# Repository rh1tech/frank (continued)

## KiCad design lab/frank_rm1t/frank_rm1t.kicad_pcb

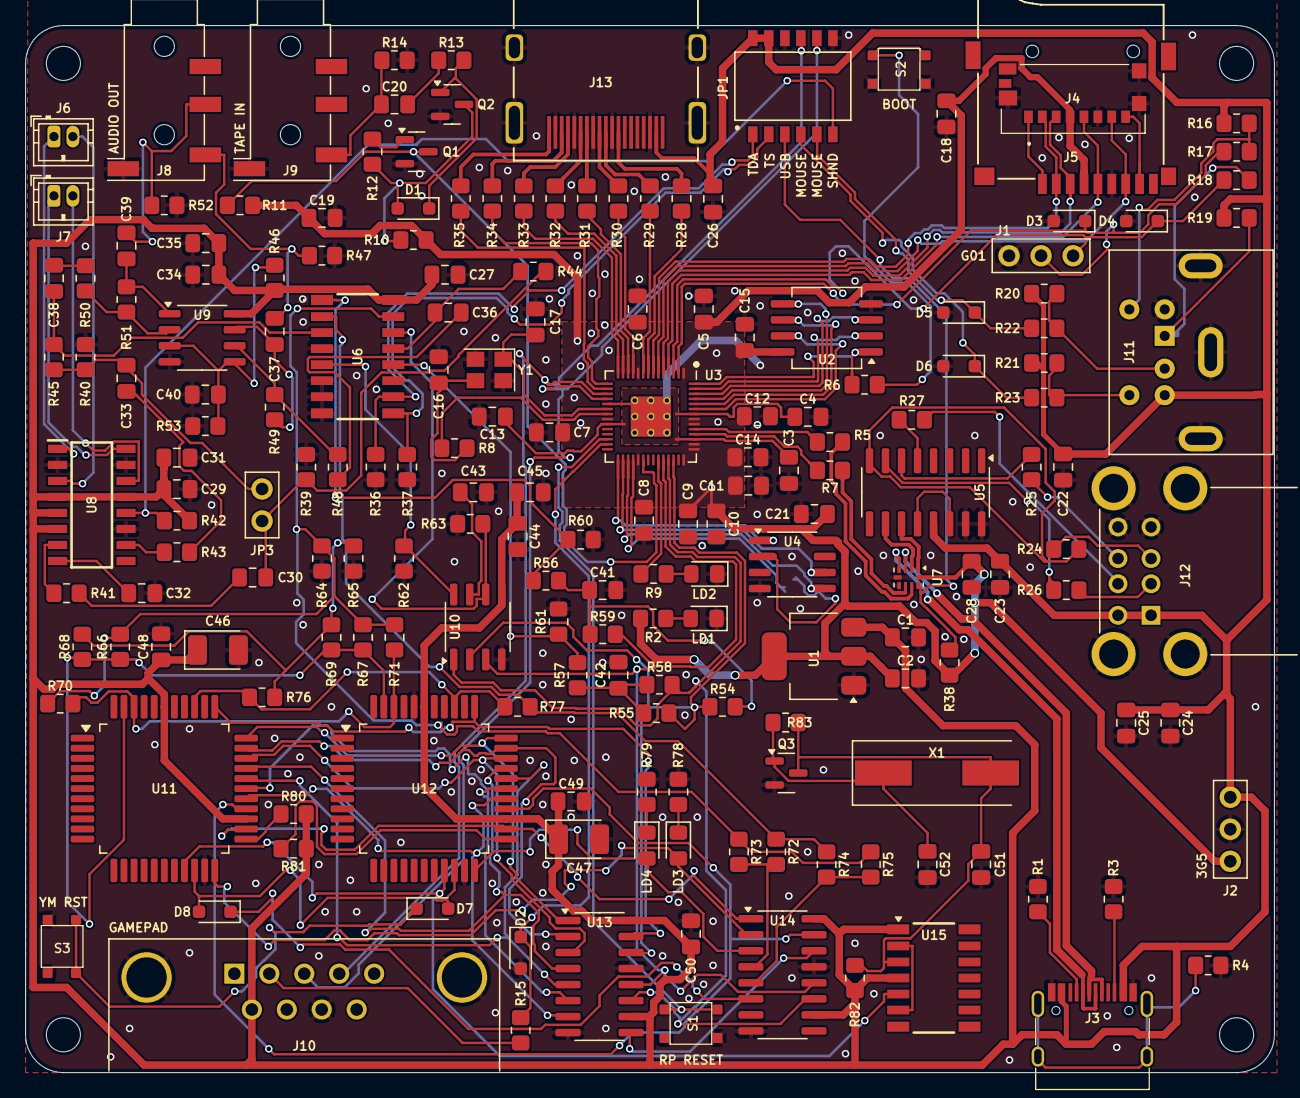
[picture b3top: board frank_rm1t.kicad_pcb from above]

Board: 2 copper layers, 99.0 x 83.0 mm, 190 parts (1 on the bottom side), 150 nets.

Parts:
C1, C2, C24, C25, C34, C36, C37, C38, C39, C40, C43, C44: 10u; Capacitor (0805)
C3, C4, C5, C6, C7, C8, C9, C10, C11, C12, C15, C18, C19, C20, C21, C22, C26, C27, C28, C32, C35, C45, C48, C49, C50: 100n; Capacitor (0805)
C13, C14, C29, C30, C33: 1u; Capacitor (0805)
C16, C17: 15p; Capacitor (0805)
C23: 4.7u; Capacitor (0805)
C31: 47u; Capacitor (0805)
C41, C42: 47n; Capacitor (0805)
C46, C47: 100u; Capacitor (3528, tantalum, polar)
C51, C52: 22p; Capacitor (0805)
D1, D7, D8: 1N4148; Diode (SOD-323)
D2, D3, D4, D5, D6: 3V3; Diode (SOD-323)
H1, H2, H3, H4: MountingHole; Mounting Hole (2.7mm)
J1: UART; Pin Header (1x03)
J2: PWR; Pin Header (1x03)
J3: USB4215-03-A; USB Type C
J4: 0475710001; MicroSD (SMD, short)
J5: 104031-0811; MicroSD (SMD, long)
J6: PAM L; Connector Female ZH 1.50mm (2 pins)
J7: PAM R; Connector Female ZH 1.50mm (2 pins)
J8, J9: PJ-320D; Jack (3.5mm, PJ-320D)
J10: D-SUB 9 Male; D-SUB (9 pin, male, top mount)
J11: MDC-036; MiniDIN (6 Pin, female)
J12: SS-52100-004; USB Type A (stacked)
J13: DC3RX19JA2; HDMI (female)
JP1: Main Jumpers; SW_DS05-127-2-06BK-SMT-TR
JP2: Jumper (Solder); Jumper (solder)
JP3: Mono; Pin Header (1x02)
LD1: Green; LED (0805)
LD2: Blue; LED (0805)
LD3, LD4: Orange; LED (0805)
Q1, Q2, Q3: BC850; SOT-23
R1, R3: 5.1K; Resistor (0805)
R2, R6, R8, R9, R11, R15, R16, R19, R20, R21, R58, R59, R78, R79, R80, R81, R82: 1K; Resistor (0805)
R4: 1M; Resistor (0805)
R5, R7: 27R; Resistor (0805)
R10, R12, R13, R36, R37, R38, R41, R42, R43, R44, R45, R46, R48, R50, R53, R56, R57, R72, R73, R74, R75: 10K; Resistor (0805)
R14, R17, R18, R22, R23: 100R; Resistor (0805)
R24, R25, R26, R27: 22R; Resistor (0805)
R28, R29, R30, R31, R32, R33, R34, R35: 270R; Resistor (0805)
R39, R40, R54, R55, R60, R61, R68, R69, R70, R71: 2K; Resistor (0805)
R47, R52: 20K; Resistor (0805)
R49, R51: 47K; Resistor (0805)
R62, R63: 470R; Resistor (0805)
R64, R65: 120R; Resistor (0805)
R66, R67, R76, R77: 4.7K; Resistor (0805)
R83: 100K; Resistor (0805)
S1: Reset; Button (SMD, 3x3mm, 1-1)
S2: Boot; Button (SMD, 3x3mm, 1-1)
S3: KLS7-TS3302; Button (SMD, 3x3mm, 1-1)
U1: NCP1117 3.3; SOT-223
U2: W25Q128JVSIQ; SOIC-8
U3: RP2040; QFN 56
U4: ESP-PSRAM32; SO-8
U5: MW7211A; SOP-16
U6: 74HC4052D; 74HC4052D653
U7: TS3USB221RSER; UQFN-10
U8: PAM8403D; SOIC127P600X175-16N
U9: LM358; SO-8
U10: TDA1387T; SO-8
U11, U12: YM3439-F
U13, U14: 74HC595; SOP-16
U15: 74HC74; 74HCT74D
X1: 3.58 MHz; Crystal (HC49-S)
Y1: 12 MHz; Crystal (3225)

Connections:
+3V3: C2.1, C5.1, C6.1, C7.1, C8.1, C9.1, C10.1, C11.1, C12.1, C14.1, C15.1, C18.2, C19.1, C21.1, C28.2, J2.1, J4.P4 (VDD), J5.4 (VDD), R2.2, R10.1, R11.1, R38.1, U1.2 (VO), U2.8 (VCC), U3.1 (IOVDD), U3.10 (IOVDD), U3.22 (IOVDD), U3.33 (IOVDD), U3.42 (IOVDD), U3.43 (ADC_AVDD), U3.44 (VREG_IN), U3.48 (USB_VDD), U3.49 (IOVDD), U4.8 (VCC), U7.10 (VCC)
/AMP_IN_L: C36.1, R44.1, U6.13 (1Z)
/AMP_IN_R: C38.1, R45.1, U6.3 (2Z)
/Audio Out/AMP_OUTL: C37.2, J8.T, R47.2
/Audio Out/AMP_OUTR: C39.2, J8.R, R52.2
/Audio Out/AMP_PAM_OUTL_M: J6.2, U8.3 (-OUTL)
/Audio Out/AMP_PAM_OUTL_P: J6.1, U8.1 (+OUT_L)
/Audio Out/AMP_PAM_OUTR_M: J7.2, U8.14 (-OUT_R)
/Audio Out/AMP_PAM_OUTR_P: J7.1, U8.16 (+OUT_R)
/Audio Out/Amplifier/ MONO_L: C30.1, JP3.1, R39.1, R44.2
/Audio Out/Amplifier/MONO_R: C33.1, JP3.2, R40.1, R45.2
/Audio Out/TS/A1: R66.2, R67.2, R68.2, R69.2, U11.43 (CHA), U12.43 (CHA)
/Audio Out/TS/B1: R70.2, R71.2, U11.42 (CHB), U12.42 (CHB)
/Audio Out/TS/BEEP: R72.2, R73.2, U14.4 (QE)
/Audio Out/TS/C1: R76.2, R77.2, U11.36 (CHC), U12.36 (CHC)
/Audio Out/TS/CLK_1.75M: U11.19 (CLOCK), U12.19 (CLOCK), U15.5 (Q)
/Audio Out/TS/DA0: U11.34 (DA0), U12.34 (DA0), U13.15 (QA)
/Audio Out/TS/DA1: U11.33 (DA1), U12.33 (DA1), U13.1 (QB)
/Audio Out/TS/DA2: U11.32 (DA2), U12.32 (DA2), U13.2 (QC)
/Audio Out/TS/DA3: U11.31 (DA3), U12.31 (DA3), U13.3 (QD)
/Audio Out/TS/DA4: U11.30 (DA4), U12.30 (DA4), U13.4 (QE)
/Audio Out/TS/DA5: U11.29 (DA5), U12.29 (DA5), U13.5 (QF)
/Audio Out/TS/DA6: U11.28 (DA6), U12.28 (DA6), U13.6 (QG)
/Audio Out/TS/DA7: U11.27 (DA7), U12.27 (DA7), U13.7 (QH)
/Audio Out/TS/SAVE: R74.2, R75.2, U14.5 (QF)
/Audio Out/TS/YM_BC1: U11.26 (BC1), U12.26 (BC1), U14.15 (QA)
/Audio Out/TS/YM_BDIR: U11.24 (BDIR), U12.24 (BDIR), U14.1 (QB)
/Audio Out/TS/YM_CS1: LD3.2 (A), U11.22 (A8), U14.2 (QC)
/Audio Out/TS/YM_CS2: LD4.2 (A), U12.22 (A8), U14.3 (QD)
/Audio Out/TS/YM_RST: D7.2 (A), D8.2 (A), U11.20 (RESET), U12.20 (RESET)
/Audio Out/TS/YM_SEL1: R80.2, U11.23 (SEL)
/Audio Out/TS/YM_SEL2: R81.2, U12.23 (SEL)
/D+: R5.1, U7.8 (D+)
/D-: R7.1, U7.7 (D-)
/DAT1: J4.P8 (DAT1), J5.8 (DAT1)
/DAT2: J4.P1 (DAT2), J5.1 (DAT2)
/GPIO0: D3.1 (K), J1.2, R17.2, U3.2 (GPIO0)
/GPIO1: D4.1 (K), J1.3, R18.2, U3.3 (GPIO1)
/GPIO2: J4.P5 (CLK), J5.5 (CLK), U3.4 (GPIO2)
/GPIO3: J4.P3 (CMD), J5.3 (CMD), U3.5 (GPIO3)
/GPIO4: J4.P7 (DAT0), J5.7 (DAT0), U3.6 (GPIO4)
/GPIO5: J4.P2 (CD/DAT3), J5.2 (DAT3/CD), U3.7 (GPIO5)
/GPIO6: R28.2, U3.8 (GPIO6)
/GPIO7: R29.2, U3.9 (GPIO7)
/GPIO8: R30.2, U3.11 (GPIO8)
/GPIO9: R31.2, U3.12 (GPIO9)
/GPIO10: R32.2, U3.13 (GPIO10)
/GPIO11: R33.2, U3.14 (GPIO11)
/GPIO12: R34.2, U3.15 (GPIO12)
/GPIO13: R35.2, U3.16 (GPIO13)
/GPIO14: J10.4, JP1.9, U3.17 (GPIO14)
/GPIO15: J10.3, JP1.8, U3.18 (GPIO15)
/GPIO16: D2.1 (K), R15.1, U3.27 (GPIO16)
/GPIO18: U3.29 (GPIO18), U4.1 (~CE)
/GPIO19: U3.30 (GPIO19), U4.6 (SCLK)
/GPIO20: U3.31 (GPIO20), U4.5 (SI/SIO)
/GPIO21: JP2.2 (B), U3.32 (GPIO21)
/GPIO22: Q1.3 (C), R11.2, U3.34 (GPIO22)
/GPIO26: R59.2, U3.38 (GPIO26_ADC0), U10.3 (DATA), U13.12 (RCLK), U14.12 (RCLK)
/GPIO27: R58.2, U3.39 (GPIO27_ADC1), U10.1 (SCLK), U13.11 (SRCLK), U14.11 (SRCLK)
/GPIO28: R54.1, R55.1, U3.40 (GPIO28_ADC2), U10.2 (LRCK), U13.14 (SER)
/HUB_D+: U5.11 (DPU), U7.1 (1D+)
/HUB_D-: U5.10 (DMU), U7.2 (1D-)
/J_TDA: JP1.1, R36.2, U6.10 (S0)
/J_TS: JP1.2, R37.2, U6.9 (S1)
/KB_CLK: J11.5, R16.2, R17.1
/KB_DATA: J11.1, R18.1, R19.2
/MS_CLK: J11.6, R21.2, R23.1
/MS_CLK_3V: D6.1 (K), JP1.4, R23.2
/MS_DATA: J11.2, R20.2, R22.1
/MS_DATA_3V: D5.1 (K), JP1.5, R22.2
/PWM_OUT_L: R57.2, R61.1, U6.12 (1Y0)
/PWM_OUT_R: R56.2, R60.1, U6.1 (2Y0)
/RP2040/GPIO25: R9.2, U3.37 (GPIO25)
/RP2040/QSPI_SCLK: U2.6 (CLK), U3.52 (QSPI_SCLK)
/RP2040/QSPI_SD0: U2.5 (DI(IO0)), U3.53 (QSPI_SD0)
/RP2040/QSPI_SD1: U2.2 (DO(IO1)), U3.55 (QSPI_SD1)
/RP2040/QSPI_SD2: U2.3 (IO2), U3.54 (QSPI_SD2)
/RP2040/QSPI_SD3: U2.7 (IO3), U3.51 (QSPI_SD3)
/RP2040/QSPI_SS: R6.1, U2.1 (~CS), U3.56 (QSPI_SS)
/RP2040/XIN: C17.1, U3.20 (XIN), Y1.1
/RP2040/XOUT: R8.1, U3.21 (XOUT)
/RUN: S1.1, U3.26 (RUN)
/SHND: JP1.6, R42.2, U8.12 (SHND)
/TDA_L: R63.2, U6.14 (1Y1), U10.6 (A_LEFT)
/TDA_R: R62.1, U6.5 (2Y1), U10.8 (A_RIGHT)
/TS_L: R64.1, R66.1, R67.1, R70.1, R71.1, R73.1, R75.1, U6.15 (1Y2)
/TS_R: R65.1, R68.1, R69.1, R72.1, R74.1, R76.1, R77.1, U6.2 (2Y2)
/USBMPXSW: JP1.3, R38.2, U7.9 (S)
/USB_D1+: R24.1, U5.8 (DP3)
/USB_D1-: R26.1, U5.7 (DM3)
/USB_D2+: R25.1, U5.6 (DP2)
/USB_D2-: R27.1, U5.5 (DM2)
/UTC_D+: J3.6 (DP1), J3.8 (DP2), U7.3 (2D+)
/UTC_D-: J3.5 (DN2), J3.7 (DN1), U7.4 (2D-)
GND: C1.2, C2.2, C3.2, C4.2, C5.2, C6.2, C7.2, C8.2, C9.2, C10.2, C11.2, C12.2, C13.2, C14.2, C15.2, C16.2, C17.2, C18.1, C19.2, C21.2, C22.2, C23.2, C24.2, C25.2, C26.2, C27.1, C28.1, C29.2, C31.2, C32.2, C34.1, C35.1, C40.1, C41.2, C42.2, C43.2, C44.2, C45.2, C46.2, C47.2, C48.2, C49.2, C50.2, C51.1, C52.1, D2.2 (A), D3.2 (A), D4.2 (A), D5.2 (A), D6.2 (A), J1.1, J2.2, J3.1 (GND), J3.12 (GND), J4.G1 (GND_1), J4.G2 (GND_2), J4.G3 (GND_3), J4.P6 (VSS), J5.6 (VSS), J8.S, J9.S, J10.8, J11.3, J12.4 (GND1), J12.8 (GND2), J12.9 (Shield), J13.2 (G_D2), J13.5 (G_D1), J13.8 (G_D0), J13.11 (G_CLK), J13.17 (G_DDC/CEC), J13.20 (SHIELD1), J13.21 (SHIELD2), J13.22 (SHIELD3), J13.23 (SHIELD4), JP1.7, JP1.10, LD1.1 (K), LD2.1 (K), Q1.2 (E), Q2.2 (E), Q3.2 (E), R1.1, R3.1, R4.2, R14.2, R36.1, R37.1, R39.2, R40.2, R47.1, R52.1, R53.1, R60.2, R61.2, R62.2, R63.1, R64.2, R65.2, R78.1, R79.1, S1.2, S2.2, S3.2, U1.1 (GND), U2.4 (GND), U3.19 (TESTEN), U3.57 (GND), U4.4 (VSS), U5.15 (GND), U5.16 (GND), U6.4 (2Y3), U6.6 (~E), U6.7 (VEE), U6.8 (GND), U6.11 (1Y3), U7.5 (GND), U7.6 (~OE), U8.2 (PGND), U8.11 (GND), U8.15 (PGND), U9.4 (V-), U10.4 (AGND), U11.21 (A9), U11.40 (VSS), U12.21 (A9), U12.40 (VSS), U13.8 (GND), U13.13 (~OE), U14.8 (GND), U14.13 (~OE), Y1.2, Y1.4
unnamed: C16.1, R8.2, Y1.3
unnamed: C20.1, J9.T, R14.1
unnamed: C20.2, R13.1
unnamed: C30.2, R41.2
unnamed: C33.2, R43.2
unnamed: C36.2, R48.2
unnamed: C37.1, R49.1, U9.7
unnamed: C38.2, R50.2
unnamed: C39.1, R51.1, U9.1
unnamed: C41.1, R54.2, R56.1, R59.1
unnamed: C42.1, R55.2, R57.1, R58.1
unnamed: D1.2 (A), Q2.3 (C), R10.2, R12.1
unnamed: D1.1 (K), Q2.1 (B), R13.2
unnamed: D7.1 (K), S3.1
unnamed: D8.1 (K), U14.6 (QG)
unnamed: J3.4 (CC1), R1.2
unnamed: J3.10 (CC2), R3.2
unnamed: J3.13 (SHIELD), R4.1
unnamed: J10.2, R15.2
unnamed: J12.3 (D1+), R24.2
unnamed: J12.2 (D1-), R26.2
unnamed: J12.7 (D2+), R25.2
unnamed: J12.6 (D2-), R27.2
unnamed: J13.12 (CLKN), R28.1
unnamed: J13.10 (CLKP), R29.1
unnamed: J13.9 (D0N), R30.1
unnamed: J13.7 (D0P), R31.1
unnamed: J13.6 (D1N), R32.1
unnamed: J13.4 (D1P), R33.1
unnamed: J13.3 (D2N), R34.1
unnamed: J13.1 (D2P), R35.1
unnamed: JP2.1 (A), U4.2 (SO/SIO)
unnamed: LD1.2 (A), R2.1
unnamed: LD2.2 (A), R9.1
unnamed: LD3.1 (K), R78.2
unnamed: LD4.1 (K), R79.2
unnamed: Q1.1 (B), R12.2
unnamed: C52.2, Q3.1 (B), R83.1, X1.1
unnamed: C51.2, Q3.3 (C), R82.1, R83.2, U15.3 (C), X1.2
unnamed: R6.2, S2.1
unnamed: R7.2, U3.46 (USB_DM)
unnamed: R5.2, U3.47 (USB_DP)
unnamed: C3.1, C4.1, C13.1, U3.23 (DVDD), U3.45 (VREG_VOUT), U3.50 (DVDD)
unnamed: U5.12 (VD33), U5.14 (VD3)
unnamed: R41.1, U8.7 (INL)
unnamed: R43.1, U8.10 (INR)
unnamed: C32.1, U8.8 (VREF)
unnamed: C40.2, R46.1, R53.2, U9.3 (+), U9.5 (+)
unnamed: R50.1, R51.2, U9.2 (-)
unnamed: R48.1, R49.2, U9.6 (-)
unnamed: C43.1, U10.7 (FLT)
unnamed: U13.9 (QH'), U14.14 (SER)
unnamed: U15.2 (D), U15.6 (~Q)
VBUS: C1.1, C22.1, C23.1, C24.1, C25.1, C26.1, C27.2, C29.1, C31.1, C34.2, C35.2, C44.1, C45.1, C46.1, C47.1, C48.1, C49.1, C50.1, J2.3, J3.2 (VBUS), J3.11 (VBUS), J10.6, J11.4, J12.1 (VBUS1), J12.5 (VBUS2), J13.18 (+5V), JP1.11, JP1.12, R16.1, R19.1, R20.1, R21.1, R42.1, R46.2, R80.1, R81.1, R82.2, U1.3 (VI), U5.13 (VDD5), U6.16 (VCC), U8.4 (PVDD), U8.5 (MUTE), U8.6 (VDD), U8.13 (PVDD), U9.8 (V+), U10.5 (VA), U11.25 (BC2), U11.39 (VDD), U12.25 (BC2), U12.39 (VDD), U13.10 (~SRCLR), U13.16 (VCC), U14.10 (~SRCLR), U14.16 (VCC), U15.1 (~R), U15.4 (~S)

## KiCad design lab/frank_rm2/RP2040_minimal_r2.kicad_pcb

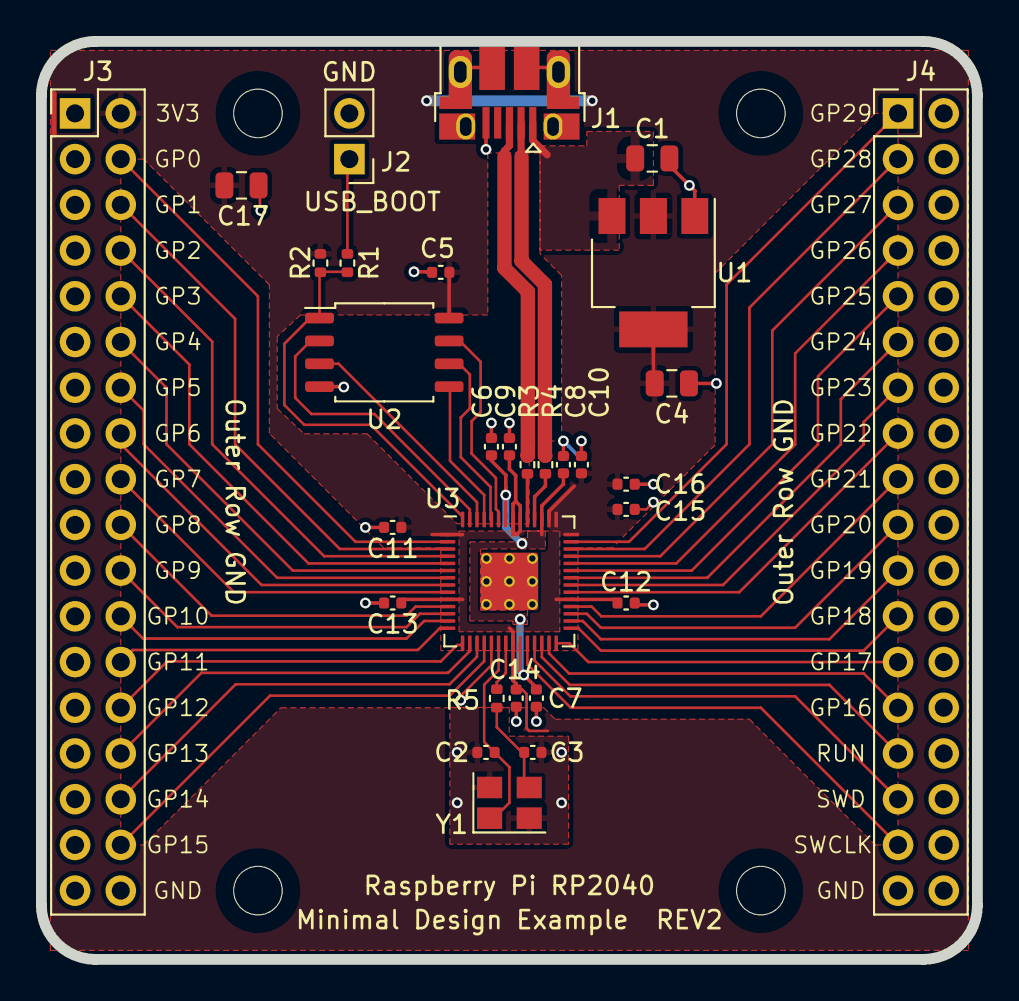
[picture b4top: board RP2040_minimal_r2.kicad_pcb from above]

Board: 2 copper layers, 52.0 x 51.0 mm, 34 parts (0 on the bottom side), 51 nets.

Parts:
C1, C4, C17: 10u; C_0805_2012Metric
C2, C3: 15p; C_0402_1005Metric
C5, C6, C7, C9, C11, C12, C13, C14, C15, C16: 100n; C_0402_1005Metric
C8, C10: 1u; C_0402_1005Metric
H1, H2, H3, H4: MountingHole; MountingHole_2.7mm_M2.5
J1: USB_B_Micro; USB_Micro-B_Amphenol_10103594-0001LF_Horizontal_modified
J2: Conn_01x02; PinHeader_1x02_P2.54mm_Vertical
J3, J4: Conn_02x18_Odd_Even; PinHeader_2x18_P2.54mm_Vertical
R1, R5: 1k; R_0402_1005Metric
R2: DNF; R_0402_1005Metric
R3, R4: 27; R_0402_1005Metric
U1: NCP1117-3.3_SOT223; SOT-223-3_TabPin2
U2: W25Q128JVS; SOIC-8_5.23x5.23mm_P1.27mm
U3: RP2040; RP2040-QFN-56
Y1: ABM8-272-T3; Crystal_SMD_3225-4Pin_3.2x2.5mm

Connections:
+1V1: C6.1, C7.1, C8.1, U3.23 (DVDD), U3.45 (VREG_VOUT), U3.50 (DVDD)
+3V3: C4.1, C5.1, C9.1, C10.1, C11.1, C12.1, C13.1, C14.1, C15.1, C16.1, C17.1, J3.2, R2.1, U1.2 (VO), U2.8 (VCC), U3.1 (IOVDD), U3.10 (IOVDD), U3.22 (IOVDD), U3.33 (IOVDD), U3.42 (IOVDD), U3.43 (ADC_AVDD), U3.44 (VREG_IN), U3.48 (USB_VDD), U3.49 (IOVDD)
/GPIO0: J3.4, U3.2 (GPIO0)
/GPIO1: J3.6, U3.3 (GPIO1)
/GPIO2: J3.8, U3.4 (GPIO2)
/GPIO3: J3.10, U3.5 (GPIO3)
/GPIO4: J3.12, U3.6 (GPIO4)
/GPIO5: J3.14, U3.7 (GPIO5)
/GPIO6: J3.16, U3.8 (GPIO6)
/GPIO7: J3.18, U3.9 (GPIO7)
/GPIO8: J3.20, U3.11 (GPIO8)
/GPIO9: J3.22, U3.12 (GPIO9)
/GPIO10: J3.24, U3.13 (GPIO10)
/GPIO11: J3.26, U3.14 (GPIO11)
/GPIO12: J3.28, U3.15 (GPIO12)
/GPIO13: J3.30, U3.16 (GPIO13)
/GPIO14: J3.32, U3.17 (GPIO14)
/GPIO15: J3.34, U3.18 (GPIO15)
/GPIO16: J4.27, U3.27 (GPIO16)
/GPIO17: J4.25, U3.28 (GPIO17)
/GPIO18: J4.23, U3.29 (GPIO18)
/GPIO19: J4.21, U3.30 (GPIO19)
/GPIO20: J4.19, U3.31 (GPIO20)
/GPIO21: J4.17, U3.32 (GPIO21)
/GPIO22: J4.15, U3.34 (GPIO22)
/GPIO23: J4.13, U3.35 (GPIO23)
/GPIO24: J4.11, U3.36 (GPIO24)
/GPIO25: J4.9, U3.37 (GPIO25)
/GPIO26_ADC0: J4.7, U3.38 (GPIO26_ADC0)
/GPIO27_ADC1: J4.5, U3.39 (GPIO27_ADC1)
/GPIO28_ADC2: J4.3, U3.40 (GPIO28_ADC2)
/GPIO29_ADC3: J4.1, U3.41 (GPIO29_ADC3)
/QSPI_SCLK: U2.6 (CLK), U3.52 (QSPI_SCLK)
/QSPI_SD0: U2.5 (DI(IO0)), U3.53 (QSPI_SD0)
/QSPI_SD1: U2.2 (DO(IO1)), U3.55 (QSPI_SD1)
/QSPI_SD2: U2.3 (IO2), U3.54 (QSPI_SD2)
/QSPI_SD3: U2.7 (IO3), U3.51 (QSPI_SD3)
/QSPI_SS: R1.1, R2.2, U2.1 (~CS), U3.56 (QSPI_SS)
/RUN: J4.29, U3.26 (RUN)
/SWCLK: J4.33, U3.24 (SWCLK)
/SWD: J4.31, U3.25 (SWD)
/USB_D+: J1.3 (D+), R3.1
/USB_D-: J1.2 (D-), R4.1
/XIN: C2.1, U3.20 (XIN), Y1.1
/XOUT: R5.1, U3.21 (XOUT)
/~USB_BOOT: J2.1, R1.2
GND: C1.2, C2.2, C3.2, C4.2, C5.2, C6.2, C7.2, C8.2, C9.2, C10.2, C11.2, C12.2, C13.2, C14.2, C15.2, C16.2, C17.2, J1.5 (GND), J1.6 (Shield), J2.2, J3.1, J3.3, J3.5, J3.7, J3.9, J3.11, J3.13, J3.15, J3.17, J3.19, J3.21, J3.23, J3.25, J3.27, J3.29, J3.31, J3.33, J3.35, J3.36, J4.2, J4.4, J4.6, J4.8, J4.10, J4.12, J4.14, J4.16, J4.18, J4.20, J4.22, J4.24, J4.26, J4.28, J4.30, J4.32, J4.34, J4.35, J4.36, U1.1 (GND), U2.4 (GND), U3.19 (TESTEN), U3.57 (GND), Y1.2, Y1.4
unnamed: C3.1, R5.2, Y1.3
unnamed: R4.2, U3.46 (USB_DM)
unnamed: R3.2, U3.47 (USB_DP)
VBUS: C1.1, J1.1 (VBUS), U1.3 (VI)

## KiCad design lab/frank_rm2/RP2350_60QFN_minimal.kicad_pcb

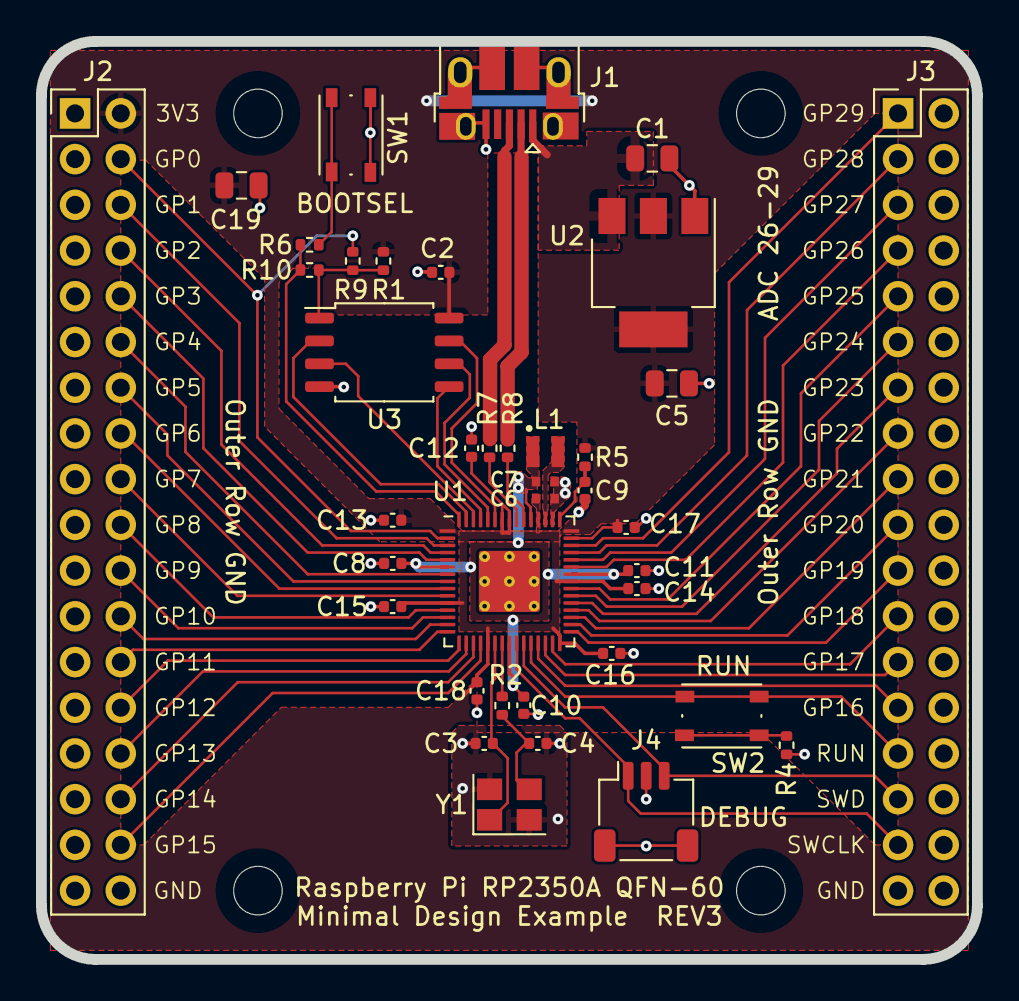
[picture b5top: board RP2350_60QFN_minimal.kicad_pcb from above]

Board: 2 copper layers, 52.0 x 51.0 mm, 43 parts (0 on the bottom side), 55 nets.

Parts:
C1, C5, C19: 10u; C_0805_2012Metric
C2, C8, C11, C12, C13, C14, C15, C16, C17, C18: 100n; C_0402_1005Metric
C3, C4: 15p; C_0402_1005Metric
C6, C7: 4.7u; C_0402_1005Metric_small_pads
C9, C10: 4.7u; C_0402_1005Metric
H1, H2, H3, H4: MountingHole; MountingHole_2.7mm_M2.5
J1: USB_B_Micro; USB_Micro-B_Amphenol_10103594-0001LF_Horizontal
J2, J3: Conn_02x18_Odd_Even; PinHeader_2x18_P2.54mm_Vertical
J4: SM03B-SRSS-TB; JST_SH_SM03B-SRSS-TB_1x03-1MP_P1.00mm_Horizontal
L1: 3.3u; L_pol_2016
R1, R9: DNF; R_0402_1005Metric
R2, R4, R6: 1k; R_0402_1005Metric
R5: 33; R_0402_1005Metric
R7, R8: 27; R_0402_1005Metric
R10: 0; R_0402_1005Metric
SW1, SW2: SW_Push; SW_Push_1P1T_NO_Vertical_Wuerth_434133025816
U1: RP2350_60QFN; RP2350-QFN-60-1EP_7x7_P0.4mm_EP3.4x3.4mm_ThermalVias
U2: NCP1117-3.3_SOT223; SOT-223-3_TabPin2
U3: W25Q128JVS; SOIC-8_5.23x5.23mm_P1.27mm
Y1: ABM8-272-T3; Crystal_SMD_3225-4Pin_3.2x2.5mm

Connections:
+1V1: C7.1, C8.1, C10.1, C11.1, L1.1, U1.6 (DVDD), U1.23 (DVDD), U1.39 (DVDD), U1.50 (VREG_FB)
+3V3: C2.1, C5.1, C6.1, C12.1, C13.1, C14.1, C15.1, C16.1, C17.1, C18.1, C19.1, J2.2, R1.1, R5.1, U1.1 (IOVDD), U1.11 (IOVDD), U1.20 (IOVDD), U1.30 (IOVDD), U1.38 (IOVDD), U1.44 (ADC_AVDD), U1.45 (IOVDD), U1.49 (VREG_VIN), U1.53 (USB_OTP_VDD), U1.54 (QSPI_IOVDD), U2.2 (VO), U3.8 (VCC)
/FLASH_SS: R1.2, R9.2, R10.2, U3.1 (~CS)
/GPIO0: J2.4, R9.1, U1.2 (GPIO0)
/GPIO1: J2.6, U1.3 (GPIO1)
/GPIO2: J2.8, U1.4 (GPIO2)
/GPIO3: J2.10, U1.5 (GPIO3)
/GPIO4: J2.12, U1.7 (GPIO4)
/GPIO5: J2.14, U1.8 (GPIO5)
/GPIO6: J2.16, U1.9 (GPIO6)
/GPIO7: J2.18, U1.10 (GPIO7)
/GPIO8: J2.20, U1.12 (GPIO8)
/GPIO9: J2.22, U1.13 (GPIO9)
/GPIO10: J2.24, U1.14 (GPIO10)
/GPIO11: J2.26, U1.15 (GPIO11)
/GPIO12: J2.28, U1.16 (GPIO12)
/GPIO13: J2.30, U1.17 (GPIO13)
/GPIO14: J2.32, U1.18 (GPIO14)
/GPIO15: J2.34, U1.19 (GPIO15)
/GPIO16: J3.27, U1.27 (GPIO16)
/GPIO17: J3.25, U1.28 (GPIO17)
/GPIO18: J3.23, U1.29 (GPIO18)
/GPIO19: J3.21, U1.31 (GPIO19)
/GPIO20: J3.19, U1.32 (GPIO20)
/GPIO21: J3.17, U1.33 (GPIO21)
/GPIO22: J3.15, U1.34 (GPIO22)
/GPIO23: J3.13, U1.35 (GPIO23)
/GPIO24: J3.11, U1.36 (GPIO24)
/GPIO25: J3.9, U1.37 (GPIO25)
/GPIO26_ADC0: J3.7, U1.40 (GPIO26_ADC0)
/GPIO27_ADC1: J3.5, U1.41 (GPIO27_ADC1)
/GPIO28_ADC2: J3.3, U1.42 (GPIO28_ADC2)
/GPIO29_ADC3: J3.1, U1.43 (GPIO29_ADC3)
/QSPI_SCLK: U1.56 (QSPI_SCLK), U3.6 (CLK)
/QSPI_SD0: U1.57 (QSPI_SD0), U3.5 (DI(IO0))
/QSPI_SD1: U1.59 (QSPI_SD1), U3.2 (DO(IO1))
/QSPI_SD2: U1.58 (QSPI_SD2), U3.3 (IO2)
/QSPI_SD3: U1.55 (QSPI_SD3), U3.7 (IO3)
/QSPI_SS: R6.1, R10.1, U1.60 (QSPI_SS)
/RUN: J3.29, SW2.2, U1.26 (RUN)
/SWCLK: J3.33, J4.1, U1.24 (SWCLK)
/SWD: J3.31, J4.3, U1.25 (SWD)
/USB_D+: J1.3 (D+), R7.1
/USB_D-: J1.2 (D-), R8.1
/VREG_AVDD: C9.1, R5.2, U1.46 (VREG_AVDD)
/VREG_LX: L1.2, U1.48 (VREG_LX)
/XIN: C3.1, U1.21 (XIN), Y1.1
/XOUT: R2.1, U1.22 (XOUT)
/~USB_BOOT: R6.2, SW1.2
GND: C1.2, C2.2, C3.2, C4.2, C5.2, C6.2, C7.2, C8.2, C9.2, C10.2, C11.2, C12.2, C13.2, C14.2, C15.2, C16.2, C17.2, C18.2, C19.2, J1.5 (GND), J1.6 (Shield), J2.1, J2.3, J2.5, J2.7, J2.9, J2.11, J2.13, J2.15, J2.17, J2.19, J2.21, J2.23, J2.25, J2.27, J2.29, J2.31, J2.33, J2.35, J2.36, J3.2, J3.4, J3.6, J3.8, J3.10, J3.12, J3.14, J3.16, J3.18, J3.20, J3.22, J3.24, J3.26, J3.28, J3.30, J3.32, J3.34, J3.35, J3.36, J4.2, J4.MP (MountPin), R4.2, SW1.1, U1.47 (VREG_PGND), U1.61 (GND), U2.1 (GND), U3.4 (GND), Y1.2, Y1.4
unnamed: C4.1, R2.2, Y1.3
unnamed: R4.1, SW2.1
unnamed: R8.2, U1.51 (USB_DM)
unnamed: R7.2, U1.52 (USB_DP)
VBUS: C1.1, J1.1 (VBUS), U2.3 (VI)

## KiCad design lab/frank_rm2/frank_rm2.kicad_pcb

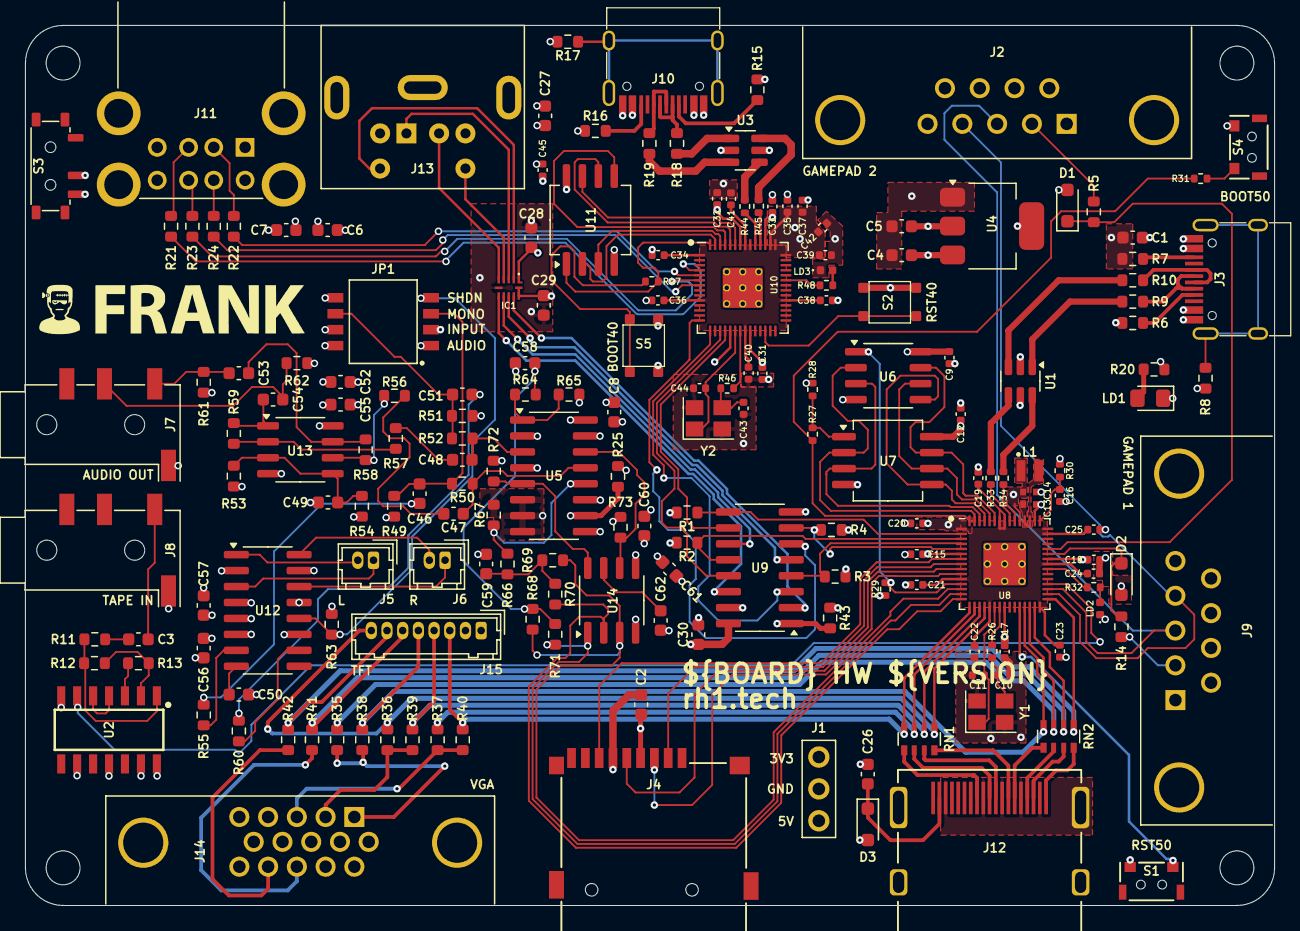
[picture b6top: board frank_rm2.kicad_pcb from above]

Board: 4 copper layers, 99.5 x 70.1 mm, 186 parts (0 on the bottom side), 157 nets.

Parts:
C1, C4, C5, C6, C7, C47, C48, C49, C52, C53, C54, C60, C62: 10u; Capacitor (0603, S)
C2, C3, C8, C26, C27, C28, C29, C30, C50, C55, C61: 100n; Capacitor (0603, S)
C9, C12, C15, C18, C19, C20, C21, C22, C23, C24, C25, C31, C32, C34, C36, C37, C38, C39, C40, C41, C42, C45: 100n; Capacitor (0402, S)
C10, C11, C43, C44: 15p; Capacitor (0402, S)
C13, C14: 4.7u; Capacitor (0402, SP)
C16, C17: 4.7u; Capacitor (0402, S)
C33, C35: 1u; Capacitor (0402, S)
C46, C51, C56: 1u; Capacitor (0603, S)
C57: 47u; Capacitor (0603, S)
C58, C59: 47n; Capacitor (0603, S)
D1, D2: 3V3; Diode (SOD-323)
D3: 1N5819WS; Diode (SOD-323)
H1, H2, H3, H4: MountingHole; Mounting Hole (2.7mm)
IC1: TXB0104RUTR
J1: PWR; Pin Header (1x03)
J2, J9: D-SUB 9 Male; D-SUB (9 pin, male, top mount)
J3, J10: USB4215-03-A; USB Type C
J4: 104031-0811; MicroSD (SMD, long)
J5: PAM L; Connector Female 1.25 JST 2P
J6: PAM R; Connector Female 1.25 JST 2P
J7, J8: PJ-320D; Jack (3.5mm, PJ-320D)
J11: SS-52100-004; USB Type A (stacked)
J12: DC3RX19JA2; HDMI (female)
J13: MDC-036; MiniDIN (6 Pin, female)
J14: D-SUB 15 Female; D-SUB (15 pin, female)
J15: Pin Header 1x08; Connector Female 1.25 JST 8P
JP1: Main Jumpers; SW_DS05-127-2-04BK-SMT-TR
L1: 3.3u; AOTA-B201610S3R3-101-T
LD1: Power; LED (0805)
LD2: Data; LED (0402, S)
LD3: Blue; LED (0402, S)
R1, R2, R3, R4, R25, R43, R50, R52, R53, R54, R55, R56, R57, R60, R63, R64, R66: 10K; Resistor (0603, S)
R5, R14, R20, R38, R39, R40, R70, R71: 1K; Resistor (0603, S)
R6, R7, R15, R16: 5.1K; Resistor (0603, S)
R8, R17: 1M; Resistor (0603, S)
R9, R10, R18, R19, R21, R22, R23, R24: 22R; Resistor (0603, S)
R11: 4.7K; Resistor (0603, S)
R12, R13: 100K; Resistor (0603, S)
R26, R31, R32, R46, R47, R48: 1K; Resistor (0402, S)
R27: 0R; Resistor (0402, S)
R28, R29: 10K; Resistor (0402, S)
R30: 33R; Resistor (0402, S)
R33, R34, R44, R45: 27R; Resistor (0402, S)
R35, R36, R37: 330R; Resistor (0603, S)
R41, R42: 100R; Resistor (0603, S)
R49, R51, R65, R67, R68, R69: 2K; Resistor (0603, S)
R58, R59: 47K; Resistor (0603, S)
R61, R62: 20K; Resistor (0603, S)
R72, R73: 470R; Resistor (0603, S)
RN1, RN2: 270R; Resistor Array (4x0603)
S1: Reset; TACT-SIDE-4623
S2: Reset; Button (SMD, 3x3mm, 1-1)
S3: MSK12C02; Switch (MSK12C02)
S4: TS-1233; TACT-SIDE-4623
S5: Boot 2040; Button (SMD, 3x3mm, 1-1)
U1, U3: USBLC6-2SC6; SOT-23-6
U2: CD4069UBM; SOIC127P600X175-14N
U4: NCP1117 3.3; SOT-223
U5: 74HC4052D; SOP-16
U6: ESP-PSRAM32; SO-8
U7: W25Q128JVS; SOIC-8
U8: RP2350; QFN 60 (RP2350A)
U9: SN74CBT3257CDR; SOP-16
U10: RP2040; QFN 56
U11: W25Q128JVSIQ; SOIC-8
U12: PAM8403D; SOP-16
U13: LM358; SO-8
U14: TDA1387T; SO-8
Y1, Y2: 12 MHz; Crystal (3225)

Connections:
+1V1: C14.1, C15.1, C17.1, C18.1, L1.1, U8.6 (DVDD), U8.23 (DVDD), U8.39 (DVDD), U8.50 (VREG_FB)
+3V3: C2.2, C5.1, C8.2, C9.1, C12.1, C13.1, C19.1, C20.1, C21.1, C22.1, C23.1, C24.1, C25.1, C29.1, C34.1, C35.1, C36.1, C37.1, C38.1, C39.1, C40.1, C41.1, C42.1, C45.1, IC1.11 (VCCB), IC1.12 (OE), J1.1, J4.4 (VDD), R1.2, R2.2, R3.2, R4.2, R20.2, R28.1, R29.2, R30.1, U2.14 (VDD), U4.2 (VO), U5.16 (VCC), U6.8 (VCC), U7.8 (VCC), U8.1 (IOVDD), U8.11 (IOVDD), U8.20 (IOVDD), U8.30 (IOVDD), U8.38 (IOVDD), U8.44 (ADC_AVDD), U8.45 (IOVDD), U8.49 (VREG_VIN), U8.53 (USB_OTP_VDD), U8.54 (QSPI_IOVDD), U10.1 (IOVDD), U10.10 (IOVDD), U10.22 (IOVDD), U10.33 (IOVDD), U10.42 (IOVDD), U10.43 (ADC_AVDD), U10.44 (VREG_IN), U10.48 (USB_VDD), U10.49 (IOVDD), U11.8 (VCC)
/AMP_IN_L: C47.1, R50.1, U5.13 (1Z)
/AMP_IN_R: C48.1, R52.1, U5.3 (2Z)
/AMP_OUT_L: C53.2, J7.T, R61.2
/AMP_OUT_R: C54.2, J7.R, R62.2
/ASW: JP1.1, R25.2, U5.10 (S0)
/Audio Out/AMP_PAM_OUTL_M: J5.2, U12.3 (-OUTL)
/Audio Out/AMP_PAM_OUTL_P: J5.1, U12.1 (+OUT_L)
/Audio Out/AMP_PAM_OUTR_M: J6.2, U12.14 (-OUT_R)
/Audio Out/AMP_PAM_OUTR_P: J6.1, U12.16 (+OUT_R)
/MONO_L: C46.1, JP1.3, R49.1, R50.2
/MONO_R: C51.1, JP1.6, R51.1, R52.2
/PS2/KB_CLK_5V: IC1.2 (A1), J13.5
/PS2/KB_DATA_5V: IC1.3 (A2), J13.1
/PS2/MS_CLK_5V: IC1.4 (A3), J13.6
/PS2/MS_DATA_5V: IC1.5 (A4), J13.2
/PS2_K_CLK: IC1.10 (B1), U9.2 (1B1)
/PS2_K_DATA: IC1.9 (B2), U9.5 (2B1)
/PS2_M_CLK: IC1.8 (B3), U9.11 (3B1)
/PS2_M_DATA: IC1.7 (B4), U9.14 (4B1)
/PSW: JP1.2, R43.2, U9.1 (S)
/PWM_OUT_L: R66.2, R67.1, U5.12 (1Y0)
/PWM_OUT_R: R64.2, R65.1, U5.1 (2Y0)
/RP1_D+: R33.1, U1.4 (I/O2)
/RP1_D-: R34.1, U1.6 (I/O1)
/RP1_GPIO0: R1.1, U8.2 (GPIO0), U9.9 (3A)
/RP1_GPIO1: R2.1, U8.3 (GPIO1), U9.12 (4A)
/RP1_GPIO2: R3.1, U8.4 (GPIO2), U9.4 (1A)
/RP1_GPIO3: R4.1, U8.5 (GPIO3), U9.7 (2A)
/RP1_GPIO4: J4.7 (DAT0), U8.7 (GPIO4)
/RP1_GPIO5: J4.2 (DAT3/CD), U8.8 (GPIO5)
/RP1_GPIO6: J4.5 (CLK), U8.9 (GPIO6)
/RP1_GPIO7: J4.3 (CMD), U8.10 (GPIO7)
/RP1_GPIO8: R29.1, U6.1 (~CE), U8.12 (GPIO8)
/RP1_GPIO9: R68.1, R69.1, U8.13 (GPIO9), U14.3 (DATA)
/RP1_GPIO10: R71.2, U8.14 (GPIO10), U14.1 (SCLK)
/RP1_GPIO11: R70.2, U8.15 (GPIO11), U14.2 (LRCK)
/RP1_GPIO12: J15.3, R40.1, RN1.4 (R4.1), U8.16 (GPIO12)
/RP1_GPIO13: R37.1, RN1.3 (R3.1), U8.17 (GPIO13)
/RP1_GPIO14: J15.4, R39.1, RN1.2 (R2.1), U8.18 (GPIO14)
/RP1_GPIO15: J15.8, R36.1, RN1.1 (R1.1), U8.19 (GPIO15)
/RP1_GPIO16: J15.5, R38.1, RN2.4 (R4.1), U8.27 (GPIO16)
/RP1_GPIO17: R35.1, RN2.3 (R3.1), U8.28 (GPIO17)
/RP1_GPIO18: J15.6, R41.2, RN2.2 (R2.1), U8.29 (GPIO18)
/RP1_GPIO19: J15.7, R42.2, RN2.1 (R1.1), U8.31 (GPIO19)
/RP1_GPIO20: J2.4, J9.4, U8.32 (GPIO20)
/RP1_GPIO21: J2.3, J9.3, U8.33 (GPIO21)
/RP1_GPIO22: U2.6 (I=*C), U8.34 (GPIO22)
/RP1_GPIO26: D2.1 (K), R14.1, U8.40 (GPIO26_ADC0)
/RP1_GPIO27: D1.1 (K), R5.1, U8.41 (GPIO27_ADC1)
/RP1_RUN: S1.1, U8.26 (RUN)
/RP2_D+: R44.1, U3.4 (I/O2)
/RP2_D-: R45.1, U3.6 (I/O1)
/RP2_GPIO2: R21.1, U10.4 (GPIO2)
/RP2_GPIO3: R22.1, U10.5 (GPIO3)
/RP2_GPIO4: R23.1, U10.6 (GPIO4)
/RP2_GPIO5: R24.1, U10.7 (GPIO5)
/RP2_GPIO11: U9.6 (2B2), U10.14 (GPIO11)
/RP2_GPIO12: U9.3 (1B2), U10.15 (GPIO12)
/RP2_GPIO14: U9.13 (4B2), U10.17 (GPIO14)
/RP2_GPIO15: U9.10 (3B2), U10.18 (GPIO15)
/RP2_RUN: S2.1, U10.26 (RUN)
/RP2040/GPIO25: R48.2, U10.37 (GPIO25)
/RP2040/QSPI_SCLK: U10.52 (QSPI_SCLK), U11.6 (CLK)
/RP2040/QSPI_SD0: U10.53 (QSPI_SD0), U11.5 (DI(IO0))
/RP2040/QSPI_SD1: U10.55 (QSPI_SD1), U11.2 (DO(IO1))
/RP2040/QSPI_SD2: U10.54 (QSPI_SD2), U11.3 (IO2)
/RP2040/QSPI_SD3: U10.51 (QSPI_SD3), U11.7 (IO3)
/RP2040/QSPI_SS: R47.1, U10.56 (QSPI_SS), U11.1 (~CS)
/RP2040/XIN: C44.1, U10.20 (XIN), Y2.1
/RP2040/XOUT: R46.1, U10.21 (XOUT)
/RP2350A/QSPI_SCLK: U6.6 (SCLK), U7.6 (CLK), U8.56 (QSPI_SCLK)
/RP2350A/QSPI_SD0: U6.5 (SI/SIO), U7.5 (DI(IO0)), U8.57 (QSPI_SD0)
/RP2350A/QSPI_SD1: U6.2 (SO/SIO), U7.2 (DO(IO1)), U8.59 (QSPI_SD1)
/RP2350A/QSPI_SD2: U6.3 (SIO2), U7.3 (IO2), U8.58 (QSPI_SD2)
/RP2350A/QSPI_SD3: U6.7 (SIO3), U7.7 (IO3), U8.55 (QSPI_SD3)
/RP2350A/QSPI_SS: R27.2, R31.1, U8.60 (QSPI_SS)
/RP2350A/VREG_AVDD: C16.1, R30.2, U8.46 (VREG_AVDD)
/RP2350A/VREG_LX: L1.2, U8.48 (VREG_LX)
/RP2350A/XIN: C11.1, U8.21 (XIN), Y1.1
/RP2350A/XOUT: R26.1, U8.22 (XOUT)
/RP2350A/~USB_BOOT: R31.2, S4.2
/SHND: JP1.4, R63.2, U12.12 (SHND)
/TDA_L: R73.2, U5.14 (1Y1), U14.6 (A_LEFT)
/TDA_R: R72.1, U5.5 (2Y1), U14.8 (A_RIGHT)
/Tape In/TAPE: C3.2, J8.T
GND: C1.2, C2.1, C4.2, C5.2, C6.2, C7.2, C8.1, C9.2, C10.2, C11.2, C12.2, C13.2, C14.2, C15.2, C16.2, C17.2, C18.2, C19.2, C20.2, C21.2, C22.2, C23.2, C24.2, C25.2, C26.2, C27.2, C28.2, C29.2, C30.1, C31.2, C32.2, C33.2, C34.2, C35.2, C36.2, C37.2, C38.2, C39.2, C40.2, C41.2, C42.2, C43.2, C44.2, C45.2, C49.1, C50.2, C52.1, C55.1, C56.2, C57.2, C58.2, C59.2, C60.2, C61.2, C62.2, D1.2 (A), D2.2 (A), IC1.6 (GND), J1.2, J2.8, J3.1 (GND), J3.12 (GND), J4.6 (VSS), J7.S, J8.S, J9.8, J10.1 (GND), J10.12 (GND), J11.4 (GND1), J11.8 (GND2), J11.9 (Shield), J12.2 (G_D2), J12.5 (G_D1), J12.8 (G_D0), J12.11 (G_CLK), J12.17 (G_DDC/CEC), J12.20 (SHIELD1), J12.21 (SHIELD2), J12.22 (SHIELD3), J12.23 (SHIELD4), J13.3, J14.0, J14.5, J14.6, J14.7, J14.8, J14.10, J15.1, JP1.5, LD1.1 (K), LD2.1 (K), LD3.1 (K), R6.1, R7.1, R8.2, R15.1, R16.1, R17.2, R25.1, R43.1, R49.2, R51.2, R54.1, R61.1, R62.1, R65.2, R67.2, R72.2, R73.1, S1.2, S2.2, S4.1, S5.2, U1.2 (GND), U2.7 (VSS), U2.9 (D14), U2.11 (E), U2.13 (F), U3.2 (GND), U4.1 (GND), U5.2 (2Y2), U5.4 (2Y3), U5.6 (~E), U5.7 (VEE), U5.8 (GND), U5.9 (S1), U5.11 (1Y3), U5.15 (1Y2), U6.4 (VSS), U7.4 (GND), U8.47 (VREG_PGND), U8.61 (GND), U9.8 (GND), U9.15 (~OE), U10.19 (TESTEN), U10.57 (GND), U11.4 (GND), U12.2 (PGND), U12.11 (GND), U12.15 (PGND), U13.4 (V-), U14.4 (AGND), Y1.2, Y1.4, Y2.2, Y2.4
GPIO25: R32.2, U8.37 (GPIO25)
unnamed: C3.1, R11.2
unnamed: C10.1, R26.2, Y1.3
unnamed: C43.1, R46.2, Y2.3
unnamed: C46.2, R55.2
unnamed: C47.2, R56.2
unnamed: C48.2, R57.2
unnamed: C51.2, R60.2
unnamed: C53.1, R58.1, U13.7
unnamed: C54.1, R59.1, U13.1
unnamed: C58.1, R64.1, R68.2, R71.1
unnamed: C59.1, R66.1, R69.2, R70.1
unnamed: C26.1, D3.1 (K), J12.18 (+5V)
unnamed: J2.2, R5.2
unnamed: J3.4 (CC1), R6.2
unnamed: J3.10 (CC2), R7.2
unnamed: J3.5 (DN2), J3.7 (DN1), R9.2
unnamed: J3.6 (DP1), J3.8 (DP2), R10.2
unnamed: J3.13 (SHIELD), R8.1
unnamed: J9.2, R14.2
unnamed: J10.4 (CC1), R15.2
unnamed: J10.10 (CC2), R16.2
unnamed: J10.5 (DN2), J10.7 (DN1), R18.2
unnamed: J10.6 (DP1), J10.8 (DP2), R19.2
unnamed: J10.13 (SHIELD), R17.1
unnamed: J11.3 (D1+), R21.2
unnamed: J11.2 (D1-), R22.2
unnamed: J11.7 (D2+), R23.2
unnamed: J11.6 (D2-), R24.2
unnamed: J12.12 (CLKN), RN1.5 (R4.2)
unnamed: J12.10 (CLKP), RN1.6 (R3.2)
unnamed: J12.9 (D0N), RN1.7 (R2.2)
unnamed: J12.7 (D0P), RN1.8 (R1.2)
unnamed: J12.6 (D1N), RN2.5 (R4.2)
unnamed: J12.4 (D1P), RN2.6 (R3.2)
unnamed: J12.3 (D2N), RN2.7 (R2.2)
unnamed: J12.1 (D2P), RN2.8 (R1.2)
unnamed: J14.1, R35.2, R38.2
unnamed: J14.2, R36.2, R39.2
unnamed: J14.3, R37.2, R40.2
unnamed: J14.13, R41.1
unnamed: J14.14, R42.1
unnamed: LD1.2 (A), R20.1
unnamed: LD2.2 (A), R32.1
unnamed: LD3.2 (A), R48.1
unnamed: R9.1, U1.1 (I/O1)
unnamed: R10.1, U1.3 (I/O2)
unnamed: R18.1, U3.1 (I/O1)
unnamed: R19.1, U3.3 (I/O2)
unnamed: R47.2, S5.1
unnamed: J10.2 (VBUS), J10.11 (VBUS), S3.2 (B)
unnamed: R11.1, R12.2, U2.1 (A)
unnamed: R13.1, U2.3 (B)
unnamed: U2.4 (H=*B), U2.5 (C)
unnamed: R12.1, R13.2, U2.2 (G-*A)
unnamed: R27.1, R28.2, U7.1 (~CS)
unnamed: R34.2, U8.51 (USB_DM)
unnamed: R33.2, U8.52 (USB_DP)
unnamed: R45.2, U10.46 (USB_DM)
unnamed: R44.2, U10.47 (USB_DP)
unnamed: C31.1, C32.1, C33.1, U10.23 (DVDD), U10.45 (VREG_VOUT), U10.50 (DVDD)
unnamed: R55.1, U12.7 (INL)
unnamed: R60.1, U12.10 (INR)
unnamed: C50.1, U12.8 (VREF)
unnamed: C49.2, R53.1, R54.2, U13.3 (+), U13.5 (+)
unnamed: R57.1, R59.2, U13.2 (-)
unnamed: R56.1, R58.2, U13.6 (-)
unnamed: C62.1, U14.7 (FLT)
VBUS: C1.1, C4.1, C6.1, C7.1, C27.1, C28.1, C30.2, C52.2, C55.2, C56.1, C57.1, C60.1, C61.1, D3.2 (A), IC1.1 (VCCA), J1.3, J2.6, J3.2 (VBUS), J3.11 (VBUS), J9.6, J11.1 (VBUS1), J11.5 (VBUS2), J13.4, J15.2, JP1.7, JP1.8, R53.2, R63.1, S3.3 (A), U1.5 (VBUS), U3.5 (VBUS), U4.3 (VI), U9.16 (VCC), U12.4 (PVDD), U12.5 (MUTE), U12.6 (VDD), U12.13 (PVDD), U13.8 (V+), U14.5 (VA)
